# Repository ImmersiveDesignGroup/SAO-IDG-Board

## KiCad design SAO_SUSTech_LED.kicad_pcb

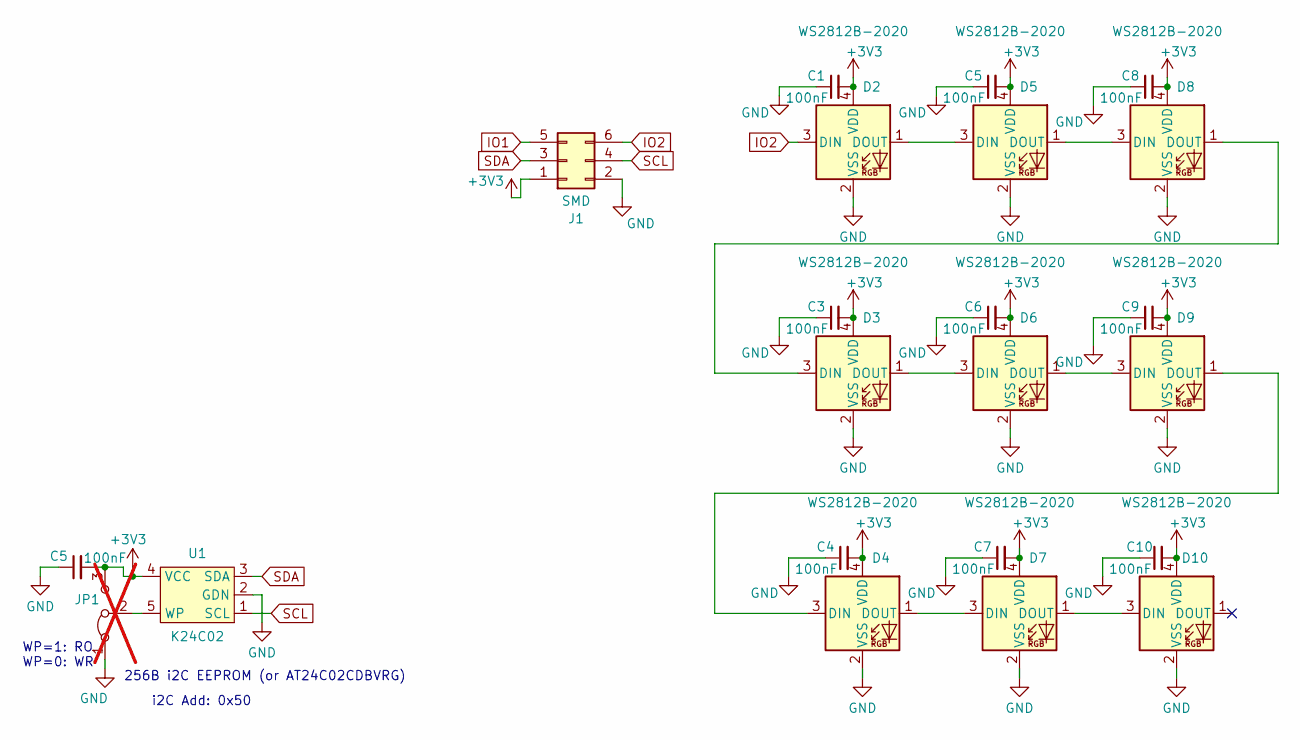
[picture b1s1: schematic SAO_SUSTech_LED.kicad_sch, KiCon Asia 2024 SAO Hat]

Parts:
C1, C3, C4, C5, C6, C7, C8, C9, C10: 100nF; C_0603_1608Metric; LCSC C6119867
D2, D3, D4, D5, D6, D7, D8, D9, D10: WS2812B-2020; LED_WS2812B-2020_PLCC4_2.0x2.0mm
J1: SMD; PinHeader_2x03_P2.54mm_Vertical_SMD; LCSC C563699
JP1: Jumper_3_Bridged12; SolderJumper-3_P1.3mm_Bridged12_RoundedPad1.0x1.5mm; not fitted
U1: K24C02; SOT-23-5; LCSC C84964

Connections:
+3V3: C1.2, C3.2, C4.2, C5.2, C6.2, C7.2, C8.2, C9.2, C10.2, D2.4 (VDD), D3.4 (VDD), D4.4 (VDD), D5.4 (VDD), D6.4 (VDD), D7.4 (VDD), D8.4 (VDD), D9.4 (VDD), D10.4 (VDD), J1.1, JP1.3 (B), U1.4 (VCC); also elsewhere on the board
GND: C1.1, C3.1, C4.1, C5.1, C6.1, C7.1, C8.1, C9.1, C10.1, D2.2 (VSS), D3.2 (VSS), D4.2 (VSS), D5.2 (VSS), D6.2 (VSS), D7.2 (VSS), D8.2 (VSS), D9.2 (VSS), D10.2 (VSS), J1.2, JP1.1 (A), U1.2 (GDN); also elsewhere on the board
IO1: J1.5
IO2: D2.3 (DIN), J1.6
unnamed: D2.1 (DOUT), D5.3 (DIN)
unnamed: D3.3 (DIN), D8.1 (DOUT)
unnamed: D3.1 (DOUT), D6.3 (DIN)
unnamed: D4.3 (DIN), D9.1 (DOUT)
unnamed: D4.1 (DOUT), D7.3 (DIN)
unnamed: D5.1 (DOUT), D8.3 (DIN)
unnamed: D6.1 (DOUT), D9.3 (DIN)
unnamed: D7.1 (DOUT), D10.3 (DIN)
unnamed: JP1.2 (C), U1.5 (WP)
SCL: J1.4, U1.1 (SCL)
SDA: J1.3, U1.3 (SDA)

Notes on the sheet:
WP=1: RO WP=0: WR
256B i2C EEPROM (or AT24C02CDBVRG)
i2C Add: 0x50

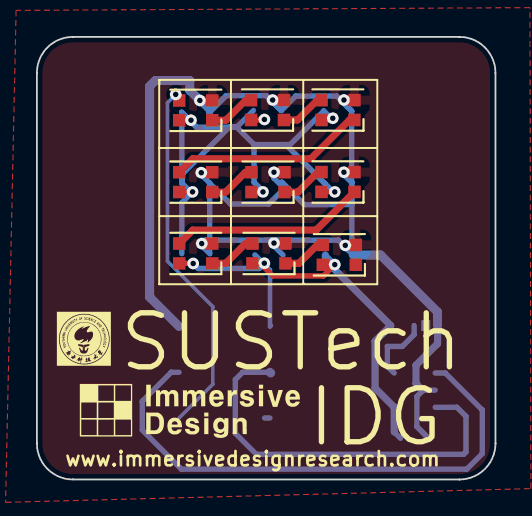
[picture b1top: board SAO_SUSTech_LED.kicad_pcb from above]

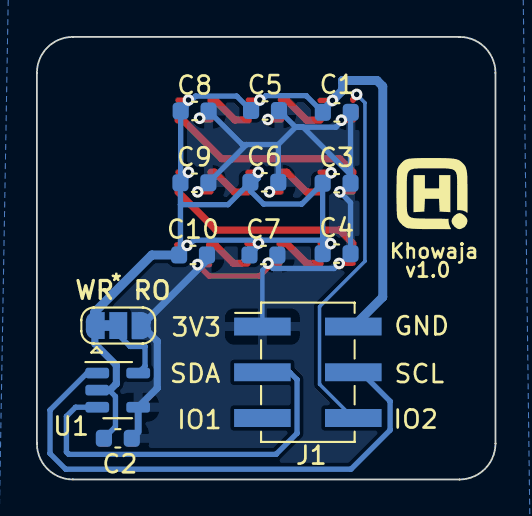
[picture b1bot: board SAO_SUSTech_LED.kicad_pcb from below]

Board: 2 copper layers, 25.5 x 24.6 mm, 22 parts (13 on the bottom side), 14 nets.

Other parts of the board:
C2: 100nF; C_0603_1608Metric

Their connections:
+3V3: C2.2; also elsewhere on the board
GND: C2.1; also elsewhere on the board
